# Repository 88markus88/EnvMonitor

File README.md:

# EnvMonitor - ESP32
This project aims to create an environmental monitoring system, using ESP32 and multiple environmental sensors and make the data visible using <B>Blynk</B> (https://blynk.io/)

The project consists of both software code and the hardware description as KiCad and (partly) Fritzing files.

It is work in progress, but already functional. Development is being done using Platformio with the Arduino platform. 

## Visualization:
Visualization is done via Blynk, a commercial service that can also be used with a local server, e.g. on a Raspberry Pi
All data that the EnvMonitor provides can be shown via the Blynk App - very simple and powerful. Since the service is cloud based, the data can be viewed at every location.
Blynk also supports a local server (e.g. on a Raspberry) - this eliminates the costs for the Blynk service.

Support is also implemented for Thingspeak (all devices) and for Virtuino (early prototype).
Thingspeak is one-way only for BME280, BME600, DS18B20, 433 MHz external sensors and CO2 sensors. Each ESP32 board can be connected to one Thingspeak channel, up to 8 data per devices (data streams) are supported by Thingspeak.

## Sensors:
So far the following sensors and devices on the following list can be included. Selection is done by modification of the #defines in *GlobalDefines.h*:
- BME280 (Temperature / Humidity / Pressure) via I2C
- BME680 (Temperature / Humidity / Pressure / Air Quality) via I2C
- DS18B20 (Temperature, up to 3 sensors) via OneWire
- MH-Z14A (CO2) via Serial2
- SenseAir S8 (CO2) via Serial2
- External temperature and humidity data from an Infactory NV5849 433MHz transmitter connected to an Arduino via Serial2
- Infactory NV5849 (433 MHz Temperature / Humidity sender) directly received via 433MHz receiver at GPIO 33. This option is supported by the software, ut not implemented on the board. 

## Devices:
- Relays / Transistor switches (2). Used for fan and for piezo buzzers.
- OLED Display 0.94" (SS1306) via I2C
- LCD Display 4 x 20 via I2C
- Button to be able to switch content of displays, or mute display light
- SD card reader via SPI

## ESP32 Hardware
The main component is an ESP32 with various peripherals attached. Communication to the peripherals is done via 
- 1Wire (DS180B20 temperature sensors)
- I2C (OLE or LCD displays, BME280 or BME 680 environment sensors
- SPI (SD card drive)
- Serial (CO2 sensors, external sensors via Arduino)
- GPIOs (button, transistor or relais)

All components are optional. They can be used in a large varity of combinations, providing that there are no confliting requirements
- Multiple devices can be combined on the I2C interface. E.g. BME280 and OLED display can be used together. Or LCD display and BME680. Or BME280 and no display.
- Up to 3 DS18B20 temperature sensors are supported. 3 connectors are provided, where they are connected in parallel. 
- Only one serial port (Serial2) is supported. Therefore only one CO2 sensor, or alternatively one Arduino, can be connected.
- Running a fan, piezo buzzer etc. via BC547 transistor, or other devices via relay, is supported by the hardware. Can also be used for a buzzer which gives an alarm uf window remains open too long.
- An internal power source can be used, which requires 7V-36V input from an external power supply.
Components that are not used do not have to be placed on the board. They can be configured out in the software via #defines

The board can be powered via USB. However, the USB power is relatively unstable. Most USB power supplies are not stabilized and should not be used, at least with multiple components connected - this can lead to brownouts and system failure. Raspberry Pi power supplies are better suited. 
Best is to use the option to add an internal DCDC converter <I>Traco TSR 1-2450E</I> that can be driven with 7-36V and provides excellent power conditioning. If this is not chosen, just leave the components (DCDC converter, capacitor, diode, terminal block) out.

It is possible to receive data from a 433 MHz transmitter via serial (e.g. received from an Arduino). (The serial port is not included in the Fritzing drawing.) 
The Arduino board, as well as it's software are described in a separate section. 

The board allows power selection for the 1Wire bus: either directly from 3.3V, or via GPIO32 of the ESP32. (In default configuration each GPIO can drive 20 mA).
This is useful to be able to completely reset the 1Wire bus - often necessary if cheap DS18B20 ("fake sensors") are being used. These have a tendency to hang after extended use, the only viable option is then to completely cut the power.

KiCad files are provided for the electrical schemas and the PCB boards. 

There is also a Fritzing file for illustration, however it is not complete: it does not contain the option to connect a 433 MHz transmitter. It also does not contain the external power supply that has been included in KiCad, and the option to power the DS18B20 sensors via digital output 32 (Jumper on J9) as an alternative to 3.3V. This may be necessary if the sensors are too unstable for continued operation, they can then optionally be reset by switching their power supply. May be necessary since most available DS18B20s are fake and prone to unstability (no data for longer periods). First option in this case is the reduction of the pulllup resistor R2 to 2.5K.

## ESP32 Code
The code is written in C++. It is intended to be flexible, to allow almost any combination of sensors and displays on the board. 
All data are sent to a Blynk server, provided that *#define isBlynk* is set.

Development platform is Platformio. The code should also compile - with minimum adaptations - on the Arduino IDE. However, Platformio is much more flexible, compile times much faster due to more efficient built. It is well worth to switch to Platformio!

In order to compile the code, the following adaptations have to be made:
1. Get the required libraries, adjust the library path in *platformio.ini* to point to your library directory
2. create your own *Credentials.h* file. A template file is provided. You need to put in the name and password for your Wifi network, this is a must to allow the ESP32 to access the network. Then insert the auth code, temperature correction data and device info strings for each device you want to use. This file can contain any number of these device definitions, each within a #ifdef /#endif construct.
3. Adapt "GlobalDefines.h" to your hardware.  
  - enter the IP address of your local Blynk server
  - set one #define for the name of the hardware configuration you want to use (one of those in the "credentials.h" file)
  - set the actual hardware definitions: use of Blynk, use of sensors, use of display etc. These hardware definitions must fit the ones set in *credentials.h*
  - determine if you want to log to a SD card and / or to the serial port
  - determine if OTA (over the air) updates shall be used
 4. modify *platformio.ini* as needed: set _default_envs_ to determine which environment is to be used. This is largely required to determine if USB  upload or OTA upload to a given IP are to be used.

## Libraries
For listing of used libraries see 
See  [Libraries](https://github.com/88markus88/EnvMonitor/blob/main/EnovMonitor680-Git/Doc/Libraries.md)

## Connectivity 
In order to transmit data to a web service the ESP32 needs to log into a local network. At present, three services can be supported
- <b>Blynk</b>: Commercial service to which the data are sent, and shown on mobile device in an app that can be configured very fleibly. The data can either be sent to the Blynk web service or to a local server. fully implemented for all data. Temperature, Humidity, Pressure etc. for all sensors are transmitted via "Virtual Pins" (see below for details). Blynk Auth Codes, which are specific for any devices and generated within the Blynk App on a mobile device, need to be put into the file <i>Credentials.h</i>
<b>Notice</b> Blynk is presently transitioning to V2.0 with much more expensive licensing models, and no local server. Makes it less desirably for hobbyist users, consider Thingspeak as an alternative.
- <b>Virtuino</b>: (Experimental) Similar solution to Blynk. However, here the device itself provides a web server into which the mobile has to log in. Only partly implemented for demonstration purposes.
- <b>Thingspeak</b>: Web service that stores sensor data and makes them available to a variety of generic mobile apps. Data for all devices and sensors (BME680, BME280, CO2 Sensors and DS18B20 can be transmitted, as well as data from 433 MHz radio sensors for temperature and humidity. Thingspeak is addressed via a https call to an address that encodes the Write API Key defined for a specific device, there can be up to 8 data channels per device. The channel to be used is encoded via  <i>thingspeakWriteAPIKey</i>. Limitation are the up to 8 data items per channel and max 4 channels (=devices) per user in the free version. Also, the data rate is limited for the free version. This is taken care of by filtering the data to thingspeak, they are only updated if a significant change has been registered.
Blynk and Thingspeak can be used in parallel on a device. 
Settings which connecitivity type is used are done in <i>GlobalDefines.h</i> via the #defines isBLYNK, isThingspeak, isVirtuino. 

### Setting the WiFi Credentials
To access the local network the ESP32 requires the network credentials, particularly the SSID and password. They could be encoded in source code, and indeed default data are included in <i>Credentials.h</i>. However, this method is very clumsy - it requires re-compile of the code every time the credentials are changed, or a new network is used. Therefore, two methods are provided to update the credentials at runtime, and store them in the Preferences (ESP32 EEPROM):
- <b>Captive Portal</b> Activated by the #define <i>isCaptivePortal</i>. If this is set, the device goes through a sequence at bootup: 
1. If Wifi login with valid credentials are stored in the preferences, these are used
2. If not, the captive portal is opened, the user can select a network and provide the password. If login with these data is possible, these credentials are stored in the preferences for future use. The default SSID for the captive portal is <i>ESP_Config</i>  , the default password is <i>12345678</i>
3. If neither works, the defaults are used (but not stores, since the network may be out temporarily)
- <b>Bluetooth</b> Activated by the #define <i>isBluetoothCredentials</i>. When activated, the ESP32 waits for 60 sec after Boot for a connection from a mobile device. In a Bluetooth terminal app on the mobile, the user can then connect to the device, and enter the credentials: <i>ssid:[id_of_your_network]<i/> <i>pass:[your_password]<i/>. These credentials are then stored in the Preferences and used in future logins

### Blynk Virtual Pins
Blynk uses the concept of __Virtual Pins__ for communication between the hardware devices and App (via the server). The list of virtual pins in actual use depends on the sensors that are implemented on a specific devices. They need to be known in order to connect the Widgets within the App to specific sensors.

See [List of Virtual Pins](https://github.com/88markus88/EnvMonitor/blob/main/EnovMonitor680-Git/Doc/BlynkVirtualPins.md)

# Arduino
PCB and Code for the Arduino Nano that can provide the data from an external 433MHz sensor is also included.
Why using and Arduino? It turns out that the Wifi used by the ESP32 interferes with the 433 MHz reception when an ESP32 is used directly. The signals are disturbed by the 100 ms heartbeat of the Wifi that cannot be changed easily. 
So a small arduino PCB and sketch have been developed to still be able to use external 433MHz sensors. This Arduino needs to be connected via cable to the ESP32. Pins used for this are +5V, GND, RxD and TxD (the latter switched between ESP32 and Arduino)
No special libraries are needed for the Arduino Sketch. 

## Parts
See [Parts List](https://github.com/88markus88/EnvMonitor/blob/main/EnovMonitor680-Git/Doc/Partslist.md)

## GPIO Pins
A number of ESP32 I/O Pins are used. 
See  [List of GPIO Pins](https://github.com/88markus88/EnvMonitor/blob/main/EnovMonitor680-Git/Doc/GPIOs.md)

## Credits
- Blynk Library from here: https://blynk.io/. Using <i>Wifi, WifiClient</i> and <i>BlynkSimpleEsp32</i> libraries
- BME 280: <i>Wire</i>, <i>Adafruit_Sensor</i> and <i>Adafruit_BME280</i> libraries
- BME 680: using <i>Zanshin_BME680</i> and <i>SPI</i> libraries by Arnd SV Zanshin, https://github.com/Zanduino/BME680  and Information from this Article https://wiki.dfrobot.com/Gravity__I2C_BME680_Environmental_Sensor__VOC,_Temperature,_Humidity,_Barometer__SKU__SEN0248 <br>
  Alternatively: BME 680 using the manufacturer supplied __BSEC__ library by Bosch Sensortec. This library is only available as pre-compiled object code. https://platformio.org/lib/show/6979/BSEC%20Software%20Library 
- NTP time using info from: https://randomnerdtutorials.com/esp32-date-time-ntp-client-server-arduino/ 
- OLED display: using <i>Adafruit_GFX</i> and <i>Adafruit_SSD1306</i> libraries
- DS18B20: using <i>OneWire</i> and <i>DallasTemperature</i> libraries
- SenseAir S8: using code from SFeli https://github.com/SFeli/ESP32_S8  
- MH-Z14A_ using code from the contributin by Mitch K https://www.hackster.io/kritch83/getting-started-with-the-mh-z14a-co2-detector-e96234 
- Infactory NV5849: based on work and code by Ray Wang https://rayshobby.net/reverse-engineer-wireless-temperature-humidity-rain-sensors-part-1/ 
- Macros for bit field manipulation by Shun Yan Cheung: http://www.mathcs.emory.edu/~cheung/Courses/255/Syllabus/1-C-intro/bit-array.html
- LCD library from Marco Schwartz: <i>LiquidCrystal_I2C</i> : https://github.com/marcoschwartz/LiquidCrystal_I2C/archive/master.zip

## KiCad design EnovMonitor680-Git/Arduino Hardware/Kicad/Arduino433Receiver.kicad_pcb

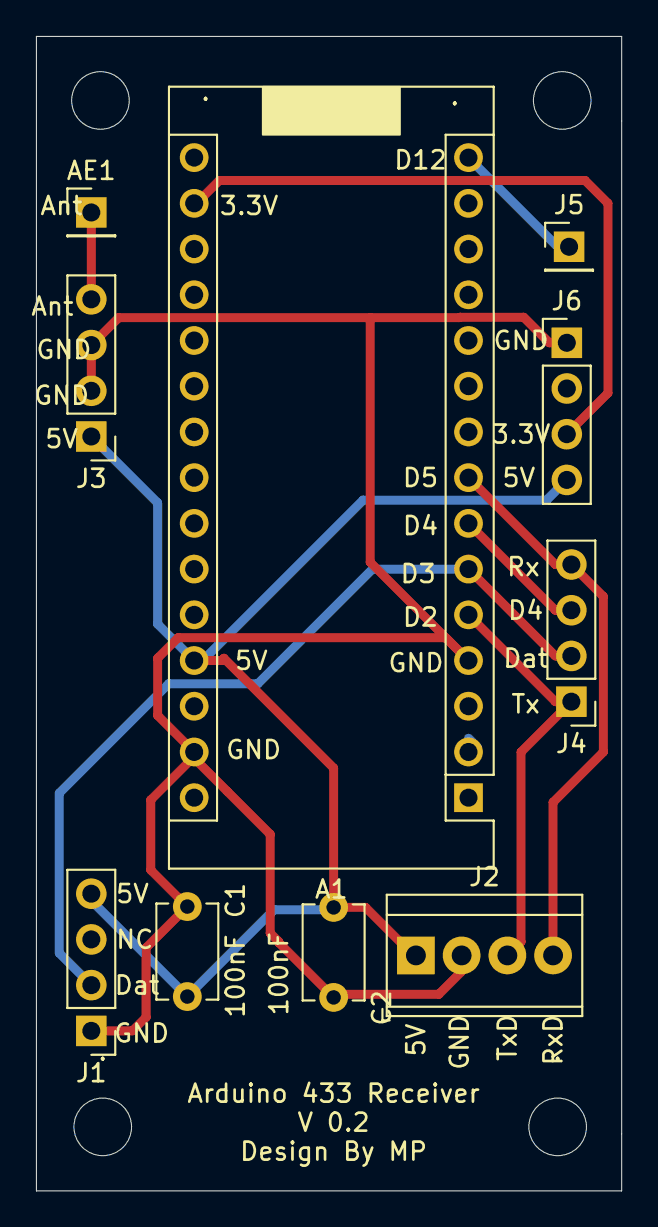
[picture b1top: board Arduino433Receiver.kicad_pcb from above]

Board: 2 copper layers, 32.5 x 64.1 mm, 14 parts (0 on the bottom side), 9 nets.

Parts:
., .#2, .#3, .#4: MountingHole_3.2mm_M3
A1: Arduino_Nano_v3.x; Arduino_Nano
AE1: Antenna; PinHeader_1x01_P2.54mm_Vertical
C1, C2: 100 nF; C_Disc_D5.1mm_W3.2mm_P5.00mm
J1: RXB6-A Pwr+Data; PinHeader_1x04_P2.54mm_Vertical
J2: Pwr + Serial; TerminalBlock_TE_282834-4_1x04_P2.54mm_Horizontal
J3: RXB6 B Ant; PinHeader_1x04_P2.54mm_Vertical
J4: Test Pins Data; PinHeader_1x04_P2.54mm_Vertical
J5: Test Pin Trigger; PinHeader_1x01_P2.54mm_Vertical
J6: Test Pins Power; PinHeader_1x04_P2.54mm_Vertical

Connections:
+5V: A1.27, C1.1, C2.1, J1.4, J2.1, J3.1, J6.4
/3.3V: A1.17, J6.3
/Ant: AE1.1, J3.4
/D2-TxD: A1.5, J2.3, J4.1
/D5-RxD: A1.8, J2.4, J4.4
/D12-Trig: A1.15, J5.1
/RXB6_Data-D3: A1.6, J1.2, J4.2
GND: A1.4, A1.29, C1.2, C2.2, J1.1, J2.2, J3.2, J3.3, J6.1
unnamed: A1.7, J4.3

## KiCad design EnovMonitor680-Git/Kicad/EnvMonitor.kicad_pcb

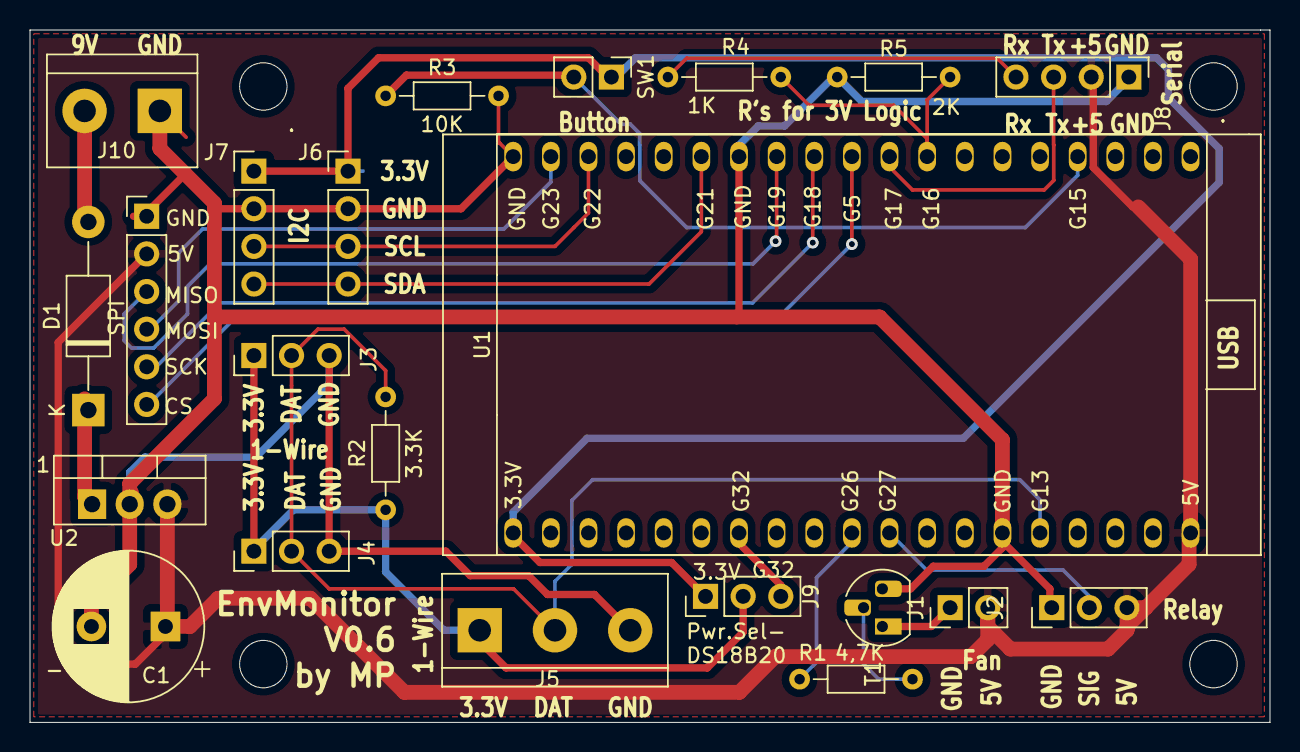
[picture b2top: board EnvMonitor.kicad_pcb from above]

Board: 2 copper layers, 83.7 x 46.7 mm, 26 parts (0 on the bottom side), 22 nets.

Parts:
., .#2, .#3, .#4: MountingHole_3.2mm_M3
C1: 470uF; CP_Radial_D10.0mm_P5.00mm
D1: 1N4001; D_DO-41_SOD81_P12.70mm_Horizontal
J1: Pinheader Fan; PinHeader_1x02_P2.54mm_Vertical
J2: Pinheader Relay; PinHeader_1x03_P2.54mm_Vertical
J3, J4: Pinheader DS18B20; PinHeader_1x03_P2.54mm_Vertical
J5: Screw_Terminal DS18B20; TerminalBlock_bornier-3_P5.08mm
J6, J7: Pinheader I2C; PinHeader_1x04_P2.54mm_Vertical
J8: Pinheader Serial; PinHeader_1x04_P2.54mm_Vertical
J9: Power Select; PinHeader_1x03_P2.54mm_Vertical
J10: Power In 9V; TerminalBlock_bornier-2_P5.08mm
R1: 4,7K; R_Axial_DIN0204_L3.6mm_D1.6mm_P7.62mm_Horizontal
R2: 3.3K; R_Axial_DIN0204_L3.6mm_D1.6mm_P7.62mm_Horizontal
R3: 10K; R_Axial_DIN0204_L3.6mm_D1.6mm_P7.62mm_Horizontal
R4: 1K; R_Axial_DIN0204_L3.6mm_D1.6mm_P7.62mm_Horizontal
R5: 2K; R_Axial_DIN0204_L3.6mm_D1.6mm_P7.62mm_Horizontal
SPI: SPI; PinHeader_1x06_P2.54mm_Vertical
SW1: SW_Push; PinHeader_1x02_P2.54mm_Vertical
T1: BC547; TO-92_HandSolder
U1: ESP32 Wroom AzDelivery; ESP32_Devkit_38Pins
U2: LM7805; TO-220-3_Vertical

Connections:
+3V3: J6.1, J7.1, J9.1, SW1.1, U1.1
+5V: C1.1, J1.2, J2.3, J8.2, SPI.2, U1.19, U2.3
+9V: D1.2, J10.2
/CS: SPI.6, U1.29
/GP13-1Wire: J3.2, J4.2, J5.2, R2.2, U1.15
/GP15-Btn: R3.1, SW1.2, U1.23
/GP17-TxD: J8.3, U1.28
/GP21-SDA: J6.4, J7.4, U1.33
/GP22-SCL: J6.3, J7.3, U1.36
/GP27-Relay: J2.2, U1.11
/GP32: J9.3, U1.7
/MISO: SPI.3, U1.31
/MOSI: SPI.4, U1.37
/RxD: J8.4, R4.1
/SCK: SPI.5, U1.30
/VCC-DS18B20: J3.1, J4.1, J5.1, J9.2, R2.1
GND: C1.2, J2.1, J3.3, J4.3, J5.3, J6.2, J7.2, J8.1, J10.1, R3.2, R5.1, SPI.1, T1.3, U1.14, U1.32, U1.38, U2.2
unnamed: D1.1, U2.1
unnamed: J1.1, T1.1
unnamed: R1.1, T1.2
unnamed: R1.2, U1.10
unnamed: R4.2, R5.2, U1.27

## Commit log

2021-05-08 Initial Commit with V0.38
2021-05-08 Delete Credentials.h
    No need for Credentials here
2021-05-08 Cleaned up, added Credentials_template.h (to be used as template for "Credentials.h" with private information)
2021-05-09 Prepare Git, credentials removed, cloud via define
2021-05-09 Initial commit of Pictures and Kicad files
2021-05-09 Fritzing picture added
2021-05-09 Added Arduino HW and SW
2021-05-10 Readme.md updated: Blynk virtual pin list added
2021-05-10 Table formatting
2021-05-10 Formatting
2021-05-10 Additional Documents added
2021-05-10 document changed
2021-05-10 BlynkVirtualPins.md created
2021-05-10 Documents for virtual pins and parts lists added
2021-05-10 Global defines: full hardware configurations set
2021-05-10 Updated readme.md - more clear documentation
2021-05-11 Improved Writing in readme.md
2021-05-12 loop to main_handler, display and main_handler via timers
2021-05-12 oled_display introduced. Only one MyBlynkTimer
2021-05-12 Testart DS18B20 with stop/start detached measurement function
2021-05-13 Improved OLED&LCD switching. Improved timer handling
2021-05-14 BME680 with BSEC library added
2021-05-14 Error corrections
2021-05-15 V0.45: BME680 BSEC lib working
2021-05-15 BME680 fully operational
2021-05-15 LCD Display improved flickering, Blynk start/restart improved
2021-05-15 Some debugging
2021-05-15 Some minor improvements in readme.md
2021-05-16 Debugging DS18B20, improved logging
2021-05-16 Debugging & Optimization of Output
2021-05-16 debugging
2021-05-16 Display off via timer implemented
2021-05-16 displays switched off via timer improved
2021-05-17 DS18B20 restart timing improved
2021-05-17 Minor debugging / output
2021-05-18 DS18B20->Blynk: compare with wrong (cal) value, corrected
2021-05-18 Updated reference to LiquidCrystal_I2C library
2021-05-21 V0.50 lauffähig bei Papa in Uslar
2021-05-21 platformio.ini with libs for both PCs correct
2021-05-24 Added List of GPIO PIns
2021-05-24 LED Heartbeat added on PIN 14 (HEARTBEATPIN)
2021-05-26 -DBOARD_HAS_PSRAM -mfix-esp32-psram-cache-issue
2021-06-02 V0.52 lauffähig ohne FanControl
2021-06-03 BME680 besser-Adresse suchen DS18B20 optimiert
2021-06-04 V0.53 BME680 restart attemts, if error -2
2021-06-18 V0.54 Extended Blynk startup if server connect fails
2021-06-24 resetBME680 triggered by bme680Status as well
2021-08-08 resetBME680 now by toggling power via relay2
2021-08-10 Counter for PowerToggles BME680 added
2021-08-13 Imroved output for BME680 power toggles
2021-10-01 NPT Time from 3 servers in sequence, ping added
2021-10-01 Improved Handling of NTP server connections, in case of failure (here due to PI-Hole having to be restarted)
2021-10-28 First Version with Virtuinio, working also for Blynk
2021-10-30 Thingspeak in time handler for DS18B20 and BME680
2021-10-31 thingspeak average introduced, first f.air quality
2021-10-31 Update README.md
    to reflect added support for thingview and for virtuino
2021-10-31 Averaging feature for thingspeak (air qual)
2021-10-31 Averaging for Thingview for all BME680 values
2021-11-11 Improved Wifi Connect Mgmt, Expressif 3.0.0->3.3.2
2021-11-11 BME680 handling: recovery from error-2 at startup
2021-11-11 Blynk%Thingspeak parallel (string too long-solved)
2021-11-13 First version with wifi credentials via bluetooth
2021-11-14 Improvements to Bluetooth credentials
2021-11-14 DS18B20 to Thingspeak averaging included
2021-11-14 Stable Version w. Bluetooth for Credentials
2021-11-16 1st version with captive portal for ssid/password
2021-11-17 Update README.md
    Added information for web services Blynk, Virtuino, Thingspeak
    Added information for Bluetooth and captive portal
2021-11-19 Captive Portal for Wifi Credentials reliable,
2021-11-20 Timeout Captive Portal. Resend Thingspeak if unsuccessful
2021-11-21 Multiple Thingspeak channels supported
2021-11-22 Captive Portal final , Breadboard w.OTA, CO2 w.Thingview
2021-11-23 Added Thingspeak for Infactory 433MHz
2021-11-23 Thingspeak added for Infactor 433 MHz sensors via serial
2021-11-24 BME280 to GeneralTestbed, improved Thingspeak timers
2021-11-25 Syslog implemented. Impr.rejection falses ExtSensors
2021-11-26 Debug Thingspeak send (3.Ch DS18 B20 vs. Ext Temp)
2021-11-29 Minor error corrections
2021-11-30 Corrected logics in Thingspeak send for DS18B20
2021-12-01 Minor error corrections. HTTP timeout set for Thingspeak
2021-12-07 Beeper & Window Open warning impl. Also bridge
2021-12-07 Update BlynkVirtualPins.md
    Added V70 and V71 with V0.85
2021-12-14 Improvements Window Open Beeper, silence Button
2021-12-15 Impr.Window Open Beeper Handling & BeepStop button
2021-12-16 Optimization of window open beeper control
2021-12-18 Send alerts to two receivers
2021-12-20 Added SenseAirS8 to GeneralTestbed
2021-12-20 SenseAirS8 working with GeneralTestbed
2022-01-02 Update README.md
    Update and minor corrections
2022-01-15 Update README.md
    Added library list in separate md file
2022-01-15 Corrected use of DS18B20 for GeneralTestbed to 1
2022-01-15 Update Libraries.md
    Added library information file
2022-01-28 Improved Timing and Output of Thingspeak data
2022-02-07 OLED output added during Wifi connect(info if not)
2022-02-12 Added screen on OLED for version, time etc.
2022-02-12 Added status, version and time for OLED display
2022-02-13 Upd ESP32 Platform to 3.5.0. Libs via lib_depths
2022-02-13 platformio.ini optimized for lib usage
2022-02-18 Impr. handling if Senseair not present, window alert
2022-02-19 Improved DS18B20 address search (duplicates)
2022-02-25 RSSI Output on display added
2022-02-28 Sending Wifi RSSI strength via V1 port
2022-03-06 Improvements in RSSI display
2022-03-06 RSSI transmitted to Thingspeak if no BME680
2022-03-10 Activate pressure correction BME280&BME680
2022-03-13 Auth removed form logs. RSSI to Thingspeak impr.
2022-03-13 Correct ntp wrong summer time with time zone string
2022-04-18 Attempt receive data from front infactory sensor
2022-08-24 Improved Glitch recognition Infactory T&H (3656f)
2022-08-24 Sniffer433 improved: doubled tolerances (particularly for 8000 ms Sync Impulses - tend to get to 8400 Added upper tolerance of 20000 to get rid of long signals (translated to -1 = 65535)
2022-10-14 Thingspeak for LCD device
2022-10-15 Update README.md
    More about Thingspeak
2022-10-16 v0:109
2022-10-17 Installed on Fujitsu Laptop
2022-10-17 Improvements on leaving out Blynk
2022-10-19 V0.111
2022-10-21 Improved display of 433MHz data on LCD
2022-10-22 BME data min 15 minutes interval
2022-10-24 Add last temp before steep rise in Thingspeak
2022-10-24 Improvements Thingspeak: quick rise, resend previous Temp
2022-10-26 Added [common_env_data] to platformio.ini
2022-10-26 Improved ENV selection via Platformio.ini variables
2022-11-10 Improvements on location dependencies. W/O Blynk
2022-11-10 Try to prevent zeroes for thingspeak p, t, h
2022-11-12 MQTT send/receive via pubsubclient lib
2022-11-16 MQTT BME680 & DS18B20-1 & logging
2022-12-18 new function mqttSendDS18B20()
2022-12-21 Improved MQTT Logging, NTP Server, MQTT Send
2023-09-18 V0.124
2023-10-22 V0.125
2023-10-23 LCD dimming made optional, new libs, new framework
2023-10-23 LCD dimming made optional, new libraries, new framework
2023-11-04 V0.128 - MQTT corrections (unique clientID)
2024-01-26 BME680 workable again
2024-01-26 V0.128 BME680 works again
